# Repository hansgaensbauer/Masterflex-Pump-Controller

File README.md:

# Masterflex Pump Controller
Bioreactor Feedback System Software and Hardware

## Pump Control Hardware

## Pump Control Connection

The pump controller accepts human-readable commands that are sent over a serial connection. To connect to the pump controller manually, use a program like [PuTTY](https://www.putty.org/) on Windows:

1. Open Device Manager, and take note of the COM ports that are listed.
2. Plug in the pump controller with a USB cable, and look to see which COM port was added (it will be something like "COM9").
3. Open PuTTY, and change "Connection Type" to "Serial".
4. Type in the COM port that you identified earlier under "Serial Line". Change the speed to "115200".
5. Click "Open". You can now type commands and hit enter to send them to the pump controller.

## Command Reference

### `setspeed [PUMP] [SPEED]`
Sets the speed of the pump specified by PUMP to the percentage specified by SPEED. Example: `setspeed 7 50` sets pump 7 to 50% speed.

### `setdir [PUMP] [DIR]`
Sets the direction of the pump specified by PUMP to counterclockwise if DIR is 0 and clockwise if DIR is 1. Example: `setdir 2 0` sets pump 7 to counterclockwise.

### `start [PUMP]`
Starts the pump specified by PUMP. Example: `start 2` starts pump 2.

### `stop [PUMP]`
Stops the pump specified by PUMP. Example: `stop 4` stops pump 4.

### `getspeed [PUMP]`
Prints the speed of the pump specified by PUMP. Example: if pump 6 is running at 35% speed, `getspeed 6` will print `35`.

### `getalarm [PUMP]`
Prints the alarm state of the pump specified by PUMP. Example: if pump 6 is under alarm, `getalarm 6` will print `Alarm!`. If it is not, it will print `Safe`.

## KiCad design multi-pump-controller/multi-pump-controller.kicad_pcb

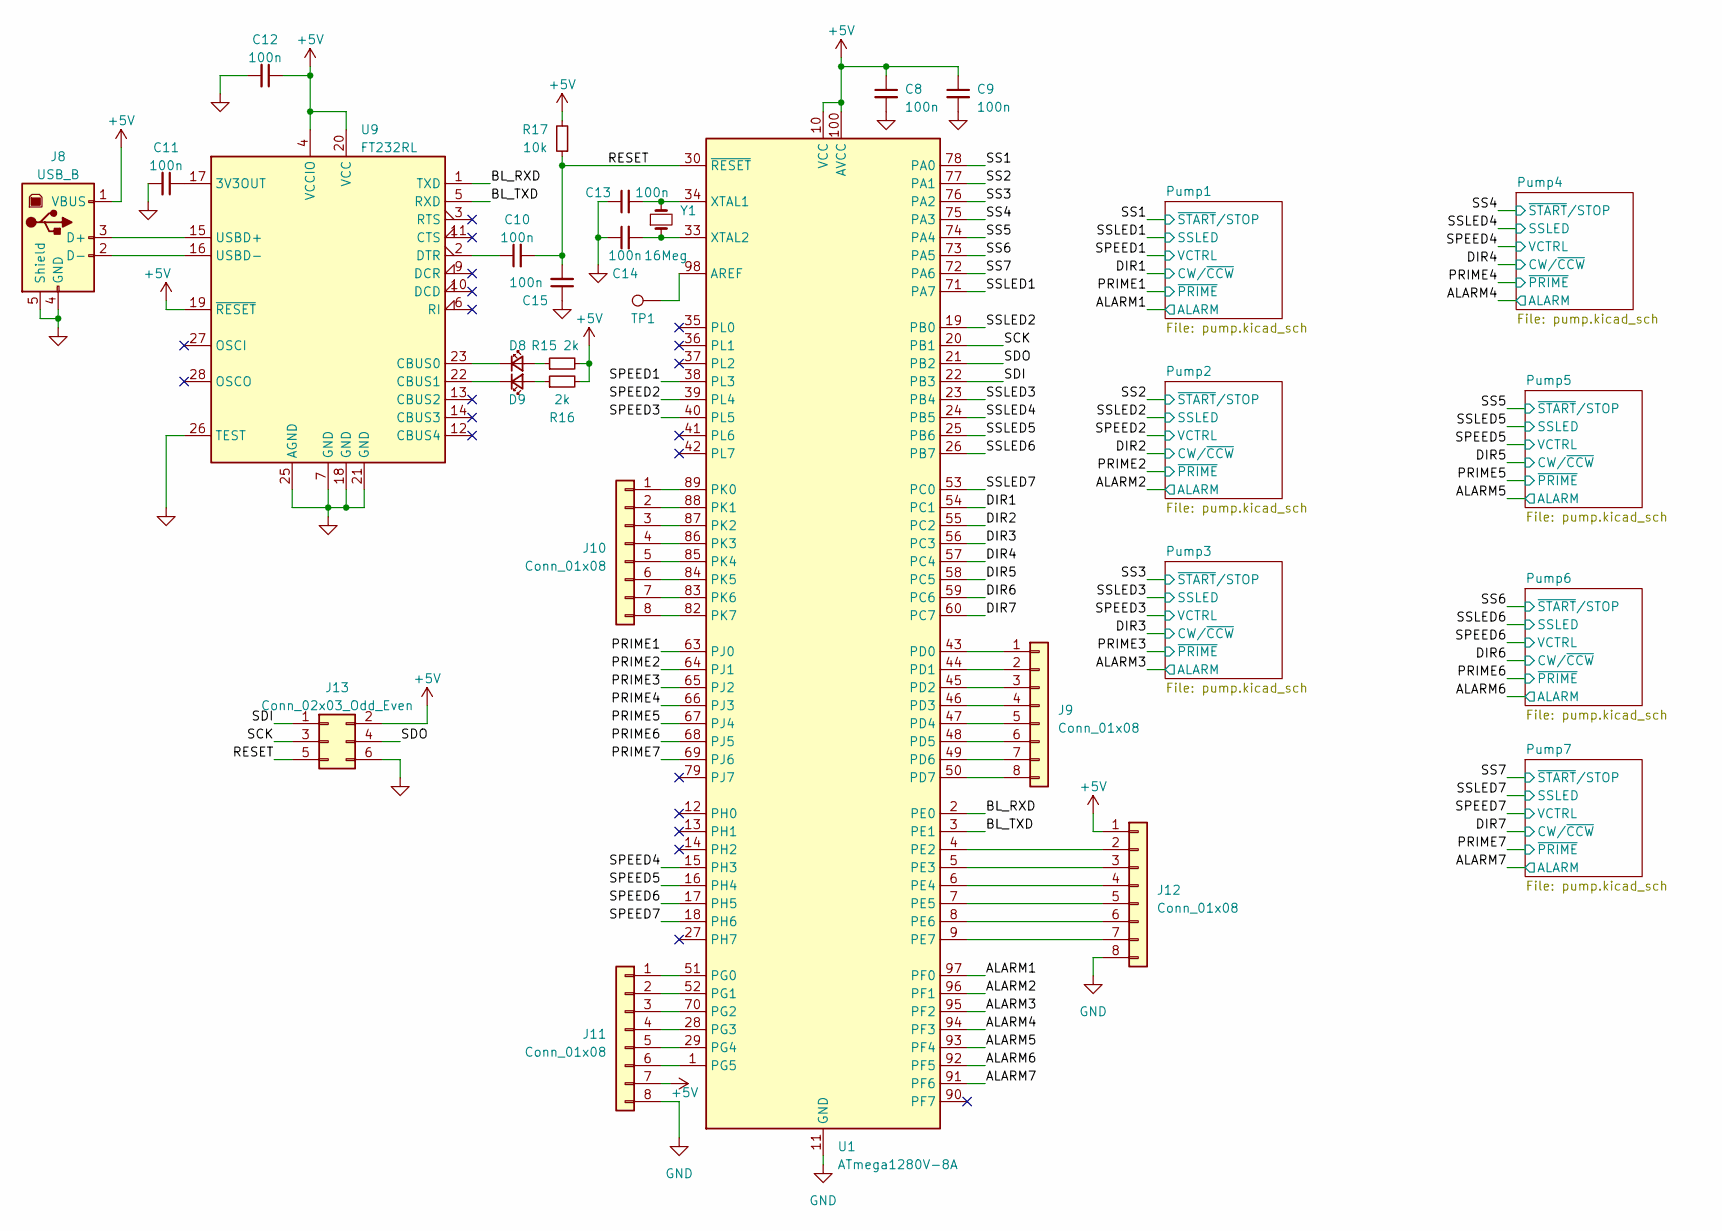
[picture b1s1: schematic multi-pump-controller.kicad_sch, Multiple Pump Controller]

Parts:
C8, C9, C10, C11, C12, C13, C14, C15: 100n; C_0603_1608Metric
D8, D9: LED_Small; LED_0805_2012Metric
J8: USB_B; USB_B_OST_USB-B1HSxx_Horizontal
J9, J10, J11, J12: Conn_01x08; PinHeader_2x04_P2.54mm_Vertical
J13: Conn_02x03_Odd_Even; PinHeader_2x03_P2.54mm_Vertical
R15, R16: 2k; R_0603_1608Metric
R17: 10k; R_0603_1608Metric
TP1: TestPoint; TestPoint_THTPad_D1.5mm_Drill0.7mm
U1: ATmega1280V-8A; TQFP-100_14x14mm_P0.5mm
U9: FT232RL; SSOP-28_5.3x10.2mm_P0.65mm
Y1: 16Meg; Crystal_HC49-4H_Vertical

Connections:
+5V: C8.1, C9.1, C12.1, J8.1 (VBUS), J11.7, J12.1, J13.2, R15.2, R16.2, R17.2, U1.10 (VCC), U1.31 (VCC), U1.61 (VCC), U1.80 (VCC), U1.100 (AVCC), U9.4 (VCCIO), U9.19 (~RESET), U9.20 (VCC); also elsewhere on the board
/ALARM1: U1.97 (PF0); also elsewhere on the board
/ALARM2: U1.96 (PF1); also elsewhere on the board
/ALARM3: U1.95 (PF2); also elsewhere on the board
/ALARM4: U1.94 (PF3); also elsewhere on the board
/ALARM5: U1.93 (PF4); also elsewhere on the board
/ALARM6: U1.92 (PF5); also elsewhere on the board
/ALARM7: U1.91 (PF6); also elsewhere on the board
/BL_RXD: U1.2 (PE0), U9.1 (TXD)
/BL_TXD: U1.3 (PE1), U9.5 (RXD)
/DIR1: U1.54 (PC1); also elsewhere on the board
/DIR2: U1.55 (PC2); also elsewhere on the board
/DIR3: U1.56 (PC3); also elsewhere on the board
/DIR4: U1.57 (PC4); also elsewhere on the board
/DIR5: U1.58 (PC5); also elsewhere on the board
/DIR6: U1.59 (PC6); also elsewhere on the board
/DIR7: U1.60 (PC7); also elsewhere on the board
/PRIME1: U1.63 (PJ0); also elsewhere on the board
/PRIME2: U1.64 (PJ1); also elsewhere on the board
/PRIME3: U1.65 (PJ2); also elsewhere on the board
/PRIME4: U1.66 (PJ3); also elsewhere on the board
/PRIME5: U1.67 (PJ4); also elsewhere on the board
/PRIME6: U1.68 (PJ5); also elsewhere on the board
/PRIME7: U1.69 (PJ6); also elsewhere on the board
/RESET: C10.2, C15.2, J13.5, R17.1, U1.30 (~RESET)
/SCK: J13.3, U1.20 (PB1)
/SDI: J13.1, U1.22 (PB3)
/SDO: J13.4, U1.21 (PB2)
/SPEED1: U1.38 (PL3); also elsewhere on the board
/SPEED2: U1.39 (PL4); also elsewhere on the board
/SPEED3: U1.40 (PL5); also elsewhere on the board
/SPEED4: U1.15 (PH3); also elsewhere on the board
/SPEED5: U1.16 (PH4); also elsewhere on the board
/SPEED6: U1.17 (PH5); also elsewhere on the board
/SPEED7: U1.18 (PH6); also elsewhere on the board
/SS1: U1.78 (PA0); also elsewhere on the board
/SS2: U1.77 (PA1); also elsewhere on the board
/SS3: U1.76 (PA2); also elsewhere on the board
/SS4: U1.75 (PA3); also elsewhere on the board
/SS5: U1.74 (PA4); also elsewhere on the board
/SS6: U1.73 (PA5); also elsewhere on the board
/SS7: U1.72 (PA6); also elsewhere on the board
/SSLED1: U1.71 (PA7); also elsewhere on the board
/SSLED2: U1.19 (PB0); also elsewhere on the board
/SSLED3: U1.23 (PB4); also elsewhere on the board
/SSLED4: U1.24 (PB5); also elsewhere on the board
/SSLED5: U1.25 (PB6); also elsewhere on the board
/SSLED6: U1.26 (PB7); also elsewhere on the board
/SSLED7: U1.53 (PC0); also elsewhere on the board
GND: C8.2, C9.2, C11.2, C12.2, C13.1, C14.1, C15.1, J8.4 (GND), J8.5 (Shield), J11.8, J12.8, J13.6, U1.11 (GND), U1.32 (GND), U1.62 (GND), U1.81 (GND), U1.99 (GND), U9.7 (GND), U9.18 (GND), U9.21 (GND), U9.25 (AGND), U9.26 (TEST); also elsewhere on the board
unnamed: D8.2 (A), R15.1
unnamed: D8.1 (K), U9.23 (CBUS0)
unnamed: D9.2 (A), R16.1
unnamed: D9.1 (K), U9.22 (CBUS1)
unnamed: J8.3 (D+), U9.15 (USBD+)
unnamed: J8.2 (D-), U9.16 (USBD-)
unnamed: J9.1, U1.43 (PD0)
unnamed: J9.2, U1.44 (PD1)
unnamed: J9.3, U1.45 (PD2)
unnamed: J9.4, U1.46 (PD3)
unnamed: J9.5, U1.47 (PD4)
unnamed: J9.6, U1.48 (PD5)
unnamed: J9.7, U1.49 (PD6)
unnamed: J9.8, U1.50 (PD7)
unnamed: J10.1, U1.89 (PK0)
unnamed: J10.2, U1.88 (PK1)
unnamed: J10.3, U1.87 (PK2)
unnamed: J10.4, U1.86 (PK3)
unnamed: J10.5, U1.85 (PK4)
unnamed: J10.6, U1.84 (PK5)
unnamed: J10.7, U1.83 (PK6)
unnamed: J10.8, U1.82 (PK7)
unnamed: J11.1, U1.51 (PG0)
unnamed: J11.2, U1.52 (PG1)
unnamed: J11.3, U1.70 (PG2)
unnamed: J11.4, U1.28 (PG3)
unnamed: J11.5, U1.29 (PG4)
unnamed: J11.6, U1.1 (PG5)
unnamed: J12.2, U1.4 (PE2)
unnamed: J12.3, U1.5 (PE3)
unnamed: J12.4, U1.6 (PE4)
unnamed: J12.5, U1.7 (PE5)
unnamed: J12.6, U1.8 (PE6)
unnamed: J12.7, U1.9 (PE7)
unnamed: TP1.1, U1.98 (AREF)
unnamed: C13.2, U1.34 (XTAL1), Y1.2
unnamed: C14.2, U1.33 (XTAL2), Y1.1
unnamed: C11.1, U9.17 (3V3OUT)
unnamed: C10.1, U9.2 (DTR)

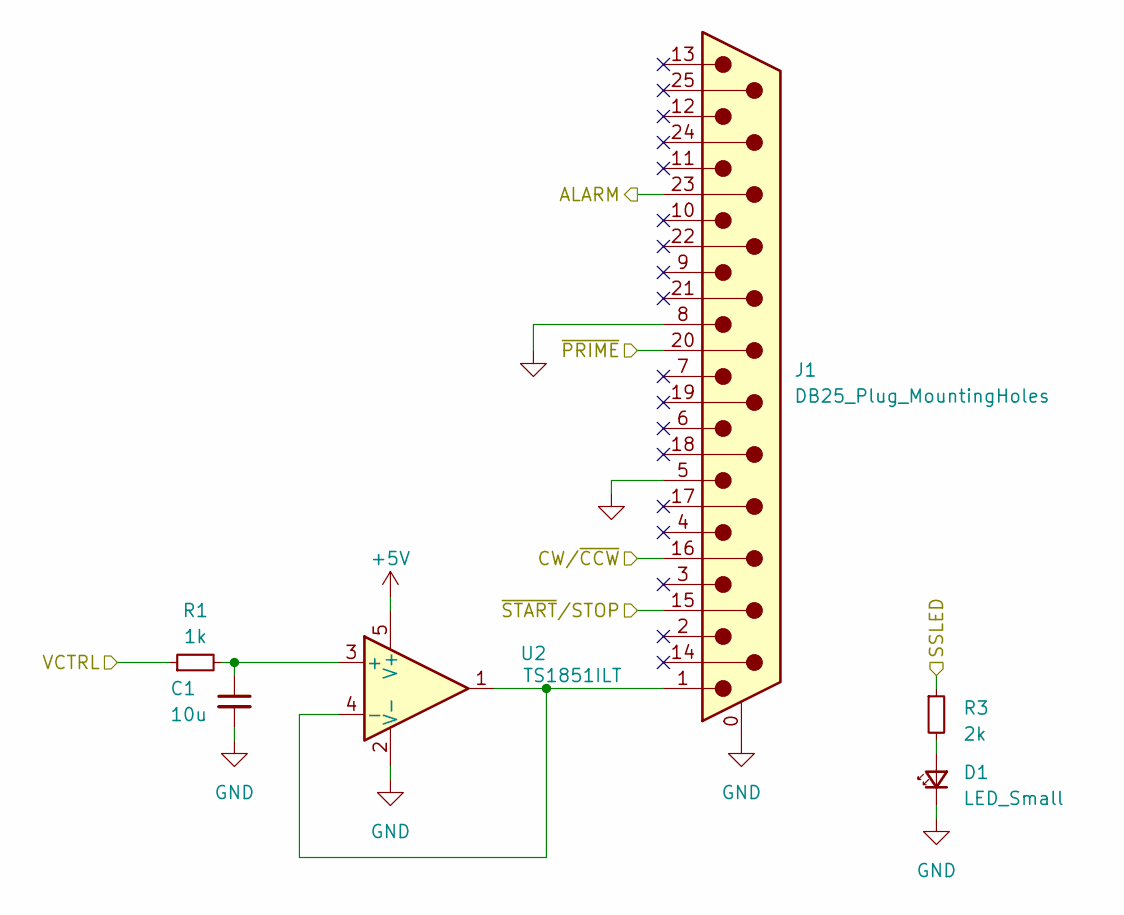
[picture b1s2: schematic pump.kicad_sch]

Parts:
C1: 10u; C_0805_2012Metric
D1: LED_Small; LED_0805_2012Metric
J1: DB25_Plug_MountingHoles; DSUB-25_Male_Vertical_P2.77x2.84mm_MountingHoles
R1: 1k; R_0603_1608Metric
R3: 2k; R_0603_1608Metric
U2: TS1851ILT; SOT-23-5

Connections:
+5V: U2.5 (V+); also elsewhere on the board
/ALARM1: J1.23; also elsewhere on the board
/DIR1: J1.16; also elsewhere on the board
/PRIME1: J1.20; also elsewhere on the board
/SPEED1: R1.1; also elsewhere on the board
/SS1: J1.15; also elsewhere on the board
/SSLED1: R3.1; also elsewhere on the board
GND: C1.2, D1.1 (K), J1.0 (PAD), J1.5, J1.8, U2.2 (V-); also elsewhere on the board
unnamed: D1.2 (A), R3.2
unnamed: C1.1, R1.2, U2.3 (+)
unnamed: J1.1, U2.1, U2.4 (-)

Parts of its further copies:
C2, C3, C4, C5, C6, C7: 10u; C_0805_2012Metric
D2, D3, D4, D5, D6, D7: LED_Small; LED_0805_2012Metric
J2, J3, J4, J5, J6, J7: DB25_Plug_MountingHoles; DSUB-25_Male_Vertical_P2.77x2.84mm_MountingHoles
R2, R5, R7, R9, R11, R13: 1k; R_0603_1608Metric
R4, R6, R8, R10, R12, R14: 2k; R_0603_1608Metric
U3, U4, U5, U6, U7, U8: TS1851ILT; SOT-23-5

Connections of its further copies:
+5V: U3.5 (V+), U4.5 (V+), U5.5 (V+), U6.5 (V+), U7.5 (V+), U8.5 (V+); also elsewhere on the board
/ALARM2: J2.23; also elsewhere on the board
/ALARM3: J3.23; also elsewhere on the board
/ALARM4: J4.23; also elsewhere on the board
/ALARM5: J5.23; also elsewhere on the board
/ALARM6: J6.23; also elsewhere on the board
/ALARM7: J7.23; also elsewhere on the board
/DIR2: J2.16; also elsewhere on the board
/DIR3: J3.16; also elsewhere on the board
/DIR4: J4.16; also elsewhere on the board
/DIR5: J5.16; also elsewhere on the board
/DIR6: J6.16; also elsewhere on the board
/DIR7: J7.16; also elsewhere on the board
/PRIME2: J2.20; also elsewhere on the board
/PRIME3: J3.20; also elsewhere on the board
/PRIME4: J4.20; also elsewhere on the board
/PRIME5: J5.20; also elsewhere on the board
/PRIME6: J6.20; also elsewhere on the board
/PRIME7: J7.20; also elsewhere on the board
/SPEED2: R2.1; also elsewhere on the board
/SPEED3: R5.1; also elsewhere on the board
/SPEED4: R7.1; also elsewhere on the board
/SPEED5: R9.1; also elsewhere on the board
/SPEED6: R11.1; also elsewhere on the board
/SPEED7: R13.1; also elsewhere on the board
/SS2: J2.15; also elsewhere on the board
/SS3: J3.15; also elsewhere on the board
/SS4: J4.15; also elsewhere on the board
/SS5: J5.15; also elsewhere on the board
/SS6: J6.15; also elsewhere on the board
/SS7: J7.15; also elsewhere on the board
/SSLED2: R4.1; also elsewhere on the board
/SSLED3: R6.1; also elsewhere on the board
/SSLED4: R8.1; also elsewhere on the board
/SSLED5: R10.1; also elsewhere on the board
/SSLED6: R12.1; also elsewhere on the board
/SSLED7: R14.1; also elsewhere on the board
GND: C2.2, C3.2, C4.2, C5.2, C6.2, C7.2, D2.1 (K), D3.1 (K), D4.1 (K), D5.1 (K), D6.1 (K), D7.1 (K), J2.0 (PAD), J2.5, J2.8, J3.0 (PAD), J3.5, J3.8, J4.0 (PAD), J4.5, J4.8, J5.0 (PAD), J5.5, J5.8, J6.0 (PAD), J6.5, J6.8, J7.0 (PAD), J7.5, J7.8, U3.2 (V-), U4.2 (V-), U5.2 (V-), U6.2 (V-), U7.2 (V-), U8.2 (V-); also elsewhere on the board
unnamed: D2.2 (A), R4.2
unnamed: D3.2 (A), R6.2
unnamed: D4.2 (A), R8.2
unnamed: D5.2 (A), R10.2
unnamed: D6.2 (A), R12.2
unnamed: D7.2 (A), R14.2
unnamed: C2.1, R2.2, U3.3 (+)
unnamed: J2.1, U3.1, U3.4 (-)
unnamed: C3.1, R5.2, U4.3 (+)
unnamed: J3.1, U4.1, U4.4 (-)
unnamed: C4.1, R7.2, U5.3 (+)
unnamed: J4.1, U5.1, U5.4 (-)
unnamed: C5.1, R9.2, U6.3 (+)
unnamed: J5.1, U6.1, U6.4 (-)
unnamed: C6.1, R11.2, U7.3 (+)
unnamed: J6.1, U7.1, U7.4 (-)
unnamed: C7.1, R13.2, U8.3 (+)
unnamed: J7.1, U8.1, U8.4 (-)

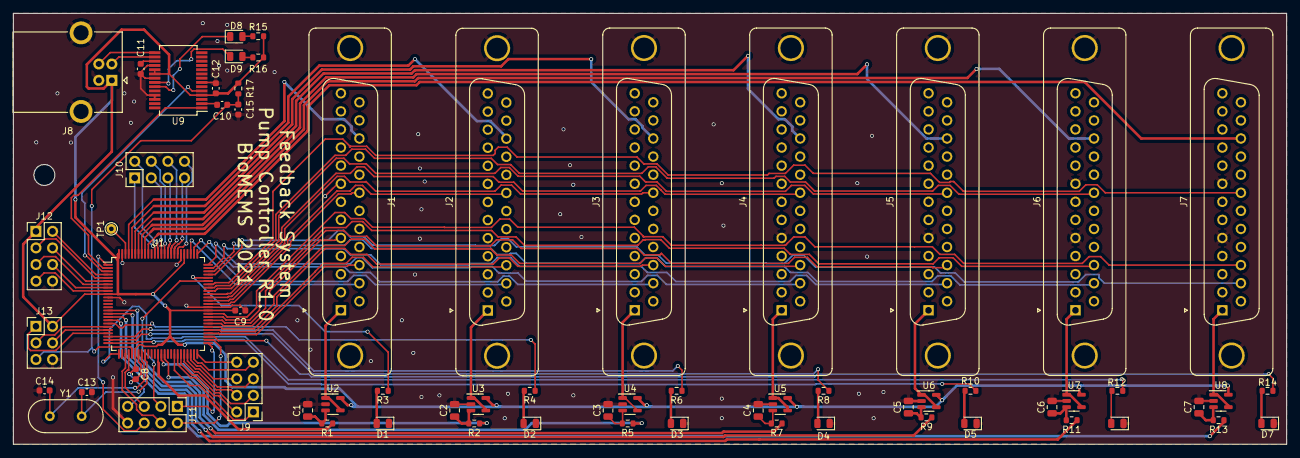
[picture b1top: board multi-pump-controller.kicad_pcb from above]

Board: 2 copper layers, 195.0 x 66.0 mm, 65 parts (0 on the bottom side), 110 nets.

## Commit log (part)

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2026-05-23 Fix readme
2026-05-23 Change Readme title
